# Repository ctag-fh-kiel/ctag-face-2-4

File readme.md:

CTAG face2|4 Audio Card, based on AD1938 codec
==============================================

This document includes board information, assembly guidelines, extensions and revision remarks, license and authors information.

Board information
-----------------
- 4 layer PCB including ground and power plane
- 10mil tracks offering close to 50Ohms impedance
- Part sizes on board are chosen to allow for hand-soldering 0603 as standard size for resistors etc.
- Used http://kicad.org/ for board design
- Board has 3 logical sections
  - Power supply (digital, analog)
     - Includes separate 3.3V digital supply and 3.3V + 5V analog supply
     - Includes boost converter that allows to run board on dual AA battery pack (3V input)
     - Standard input voltage at P201 should be +5V, see assembly options below
  - Codec including reset circuitry and digital I/O
  - Analog I/O
     - We checked several different single supply rail-to-rail OP Amps, where the cheap TLV272 performed pretty well, similar to the LMV722
- Codec and analog section is mainly based on Analog Devices reference design http://www.analog.com/media/en/technical-documentation/user-guides/UG-087.pdf

Assembly
-------------
- face2|4 BOM shared at Mouser
  - http://www.mouser.com/tools/projectcartsharing.aspx Access ID: 43007b9807
- Start with assembling the power supply sections
  - Several options for configuration are possible
     - A: Simplest possible, assemble only U203, U204, bypass U201 with JP201, bypass L202 with JP206, bypass L203 with JP207, assemble FB202, place JP204. Input voltage can be anything from 6-9V in this configuration.
     - B: No dedicated 3.3V digital do not assemble U202, assemble FB202, input voltage can be anything 2.4V-5V, boost converter will generate 5.5V for low-noise LDOs
     - C: With dedicated 3.3V digital supply, default in schematic, input voltage should be 5V
  - Check if power supply works by observing the LEDs
- Continue with codec, digital I/O and bias circuitry
  - Assembling only C311, C312 + JP301 is enough, using CM bias for test purposes
  - Test codec with microcontroller system, check at R602 R605 for signal output	
- Finally assemble analog section
  - May play around with some different OP amps

Extensions
-------------
- Created cape for Beagle Bone Green / Black including digital isolators to reduce noise (BBG-cape)
- Beagle Board X15 break out adapters for Hirose headers

Revisions
-------------
- face2|4
  - Rev. A2
     - Fixed polarity bug on IN2 at ADC2RP ADC2RN
    - Known Bugs: 
	 - none
	 - Rev. A has polarity bug on IN2
  - Todos for next Rev.
     - Possibly simplify power supply
     - Remove option to choose bias output from codec --> simplify board
	 - Option for balanced inputs
	 - Optimize pins on P1001 to improve routing, i.e. less vias on high speed digital lines, preserve impedance
- BBG-cape
  - Rev. A 
     - Initial Revision
    - Known Bugs: -
- X15 adaptor
  - Rev. A
     - Initial Revision, thanks to Michael Welling for review
	 
License
-------
This work is licensed under the Creative Commons Attribution-NonCommercial-ShareAlike 4.0 International License. 
To view a copy of this license, visit http://creativecommons.org/licenses/by-nc-sa/4.0/.
Anyone re-using this design needs to attribute to authors and http://www.creative-technologies.de website.

Authors
-------
- Robert Manzke (robert.manzke@fh-kiel.de), PCB Design
- Henrik Langer (henrik.langer@student.fh-kiel.de), Component Selection, Driver Development for Beagle Bone Series

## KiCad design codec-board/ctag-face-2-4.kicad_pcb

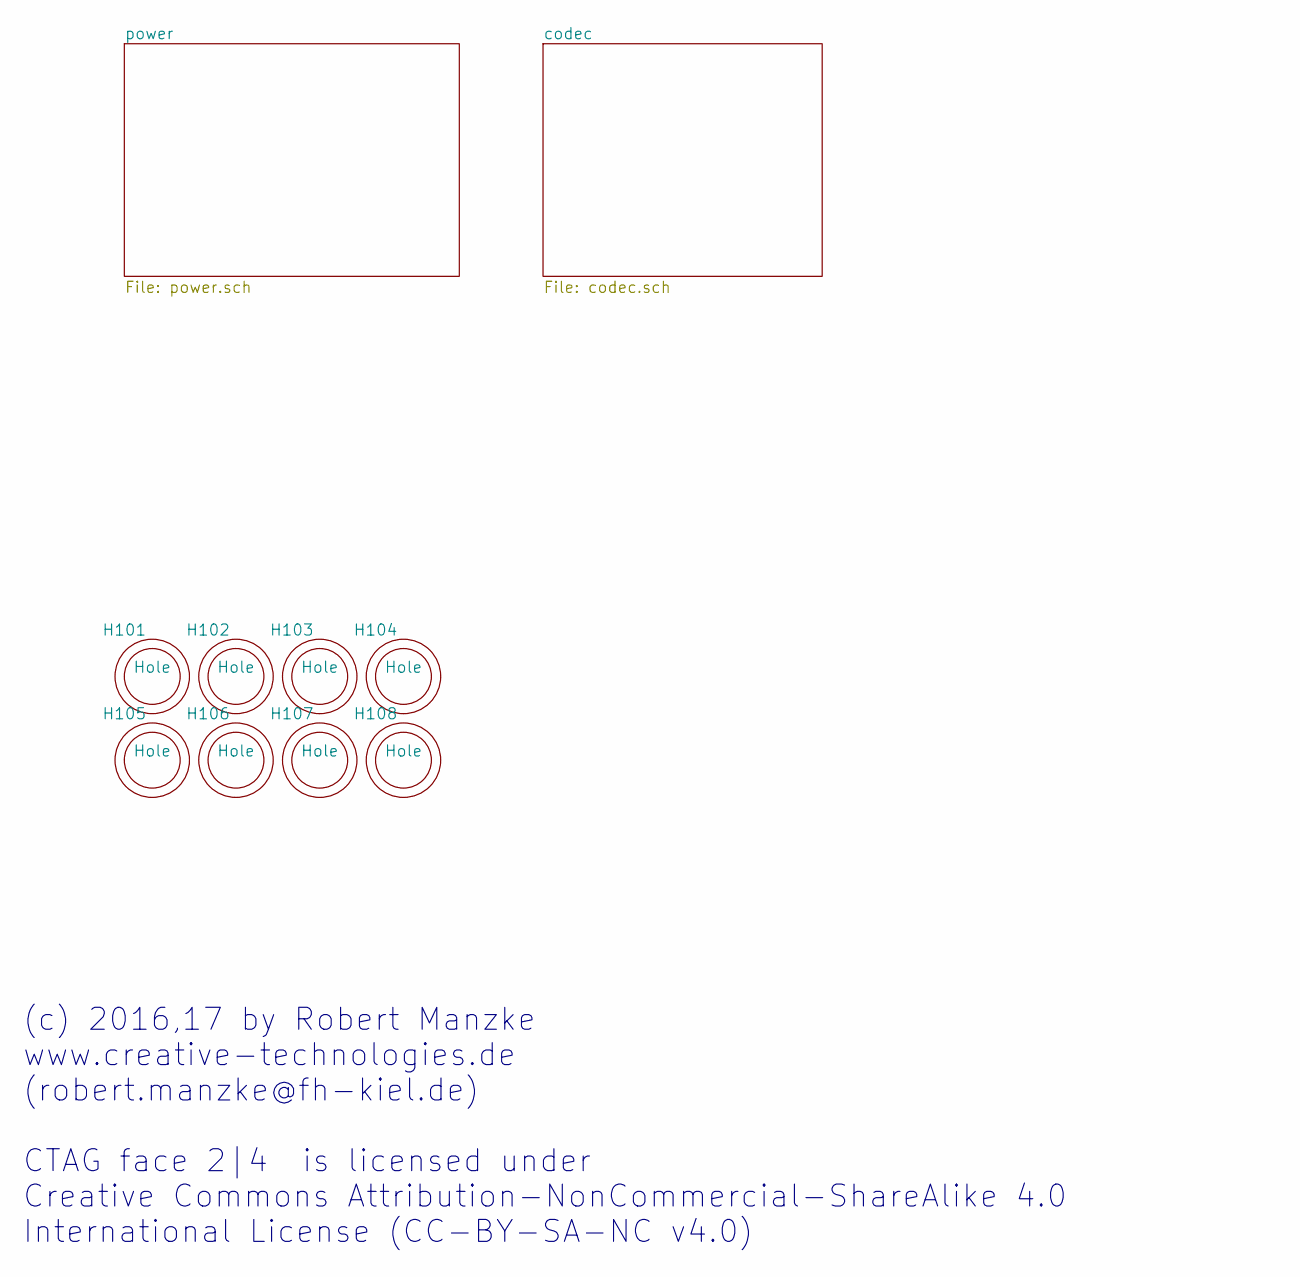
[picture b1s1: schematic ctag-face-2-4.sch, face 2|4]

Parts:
H101, H102, H103, H104, H105, H106, H107, H108: Hole; Hole_3mm

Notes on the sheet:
(c) 2016,17 by Robert Manzke www.creative-technologies.de (robert.manzke@fh-kiel.de) CTAG face 2|4 is licensed under Creative Commons Attribution-NonCommercial-ShareAlike 4.0 International License (CC-BY-SA-NC v4.0)

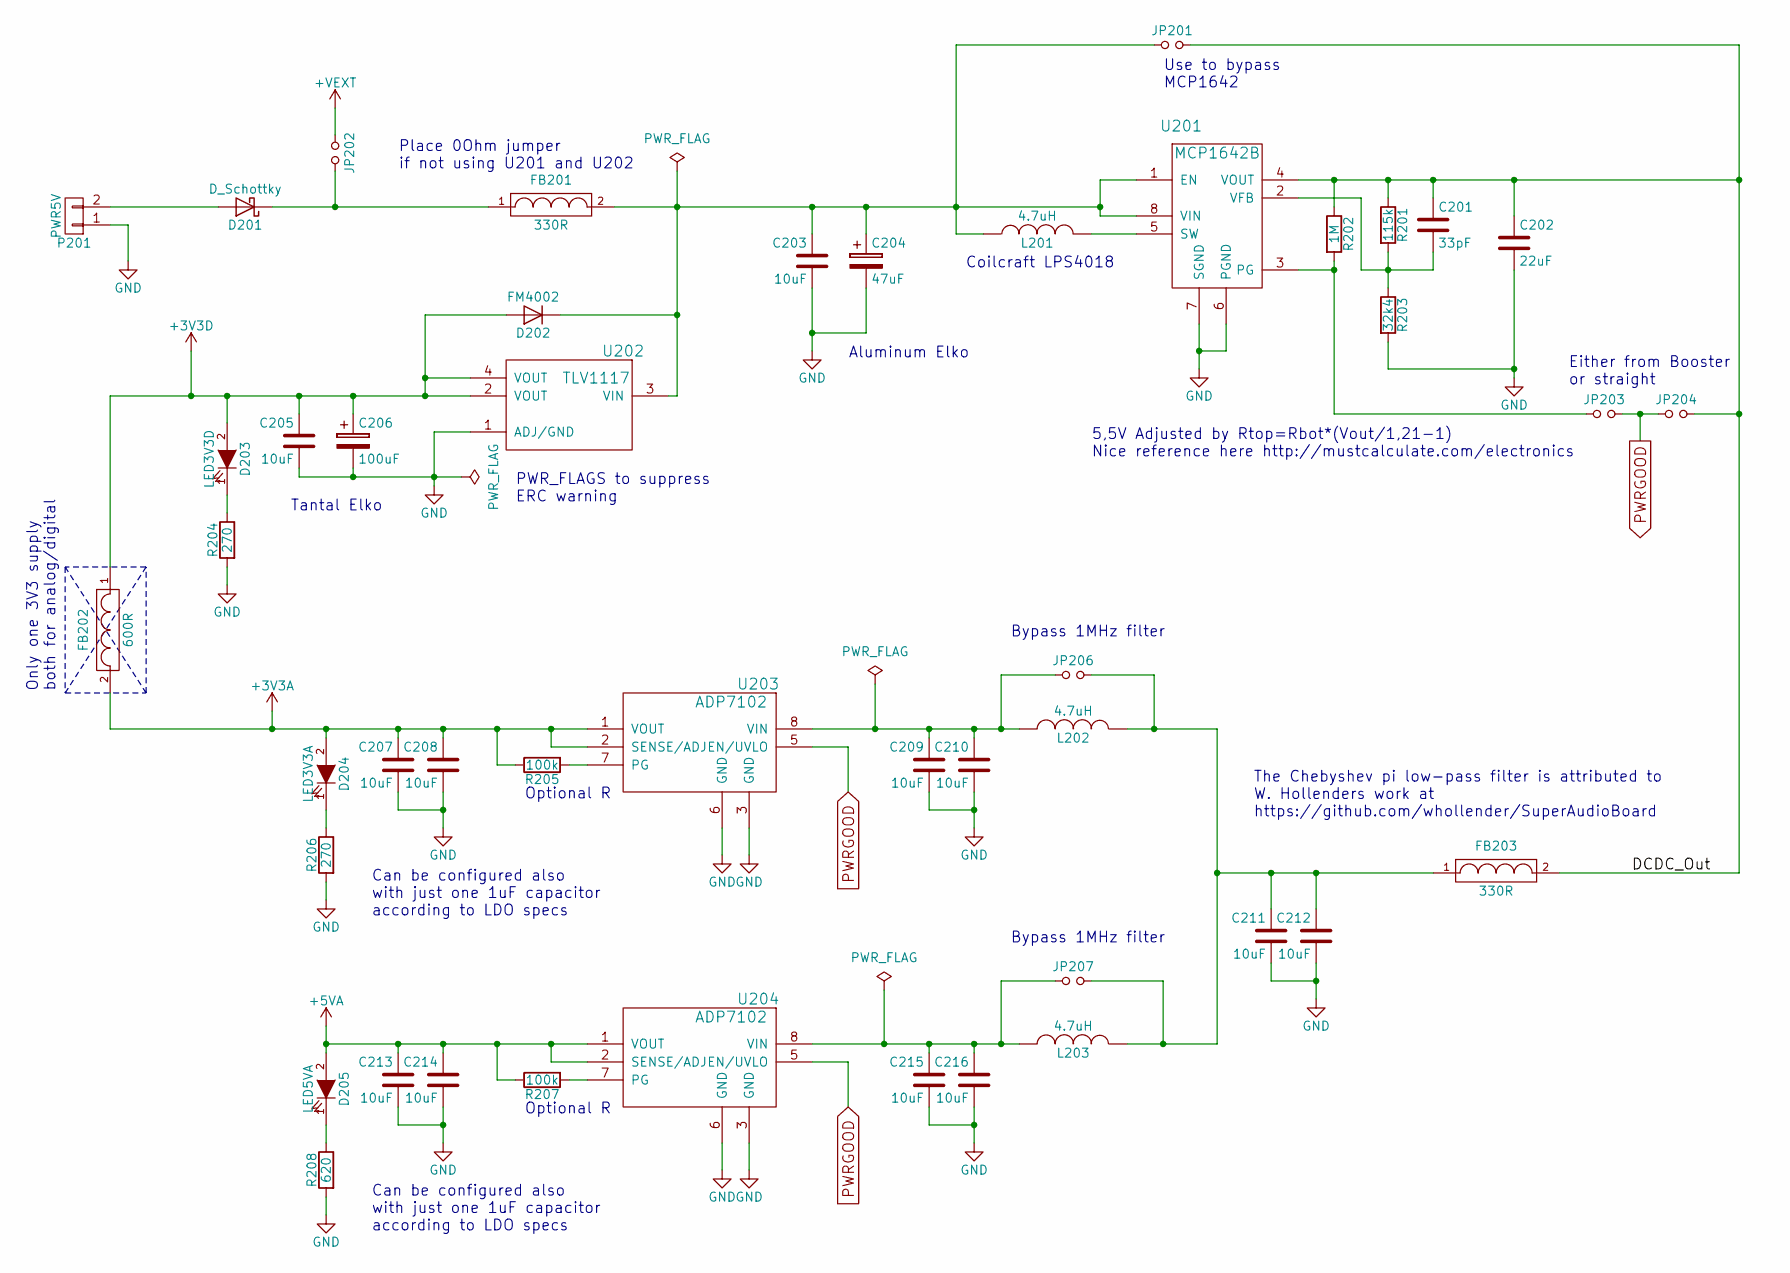
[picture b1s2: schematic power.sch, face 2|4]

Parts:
C201: 33pF; C_0603_HandSoldering
C202: 22uF; C_1210_HandSoldering
C203, C205, C207, C208, C209, C210, C211, C212, C213, C214, C215, C216: 10uF; C_1210_HandSoldering
C204: 47uF; c_elec_6.3x5.7
C206: 100uF; TantalC_SizeB_EIA-3528_HandSoldering
D201: D_Schottky; SOD-123
D202: FM4002; Diode-Universal-SMA-SMB_Handsoldering
D203: LED3V3D; LED-1206
D204: LED3V3A; LED-1206
D205: LED5VA; LED-1206
FB201, FB203: 330R; R_0805_HandSoldering
FB202: 600R; R_0805_HandSoldering
JP201, JP206, JP207: Jumper_NO_Small; R_0805_HandSoldering
JP202: Jumper_NO_Small; Pin_Header_Straight_1x02
JP203, JP204: Jumper_NO_Small; R_0603_HandSoldering
L201, L202, L203: 4.7uH; LPS4018
P201: PWR5V; Pin_Header_Straight_1x02
R201: 115k; R_0603_HandSoldering
R202: 1M; R_0603_HandSoldering
R203: 32k4; R_0603_HandSoldering
R204, R206: 270; R_0603_HandSoldering
R205, R207: 100k; R_0603_HandSoldering
R208: 620; R_0603_HandSoldering
U201: MCP1642B; MSOP-8_3x3mm_Pitch0.65mm
U202: TLV1117; SOT-223
U203, U204: ADP7102; SOIC-8_3.9x4.9mm_Pitch1.27mm

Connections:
+3V3A: C207.1, C208.1, D204.2 (A), FB202.2, R205.1, U203.1 (VOUT), U203.2 (SENSE/ADJ); also elsewhere on the board
+3V3D: C205.1, C206.1, D202.2 (A), D203.2 (A), FB202.1, U202.2 (VOUT), U202.4 (VOUT); also elsewhere on the board
+5VA: C213.1, C214.1, D205.2 (A), R207.1, U204.1 (VOUT), U204.2 (SENSE/ADJ); also elsewhere on the board
+VEXT: JP202.1; also elsewhere on the board
/power/DCDC_Out: C201.1, C202.1, FB203.2, JP201.2, JP204.2, R201.1, R202.1, U201.4 (VOUT)
GND: C202.2, C203.2, C204.2, C205.2, C206.2, C207.2, C208.2, C209.2, C210.2, C211.2, C212.2, C213.2, C214.2, C215.2, C216.2, P201.1, R203.2, R204.2, R206.2, R208.2, U201.6 (PGND), U201.7 (SGND), U202.1 (ADJ/GND), U203.3 (GND), U203.6 (GND), U204.3 (GND), U204.6 (GND); also elsewhere on the board
unnamed: C201.2, R201.2, R203.1, U201.2 (VFB)
unnamed: C203.1, C204.1, D202.1 (K), FB201.2, JP201.1, L201.1, U201.1 (EN), U201.8 (VIN), U202.3 (VIN)
unnamed: C209.1, C210.1, JP206.1, L202.2, U203.8 (VIN)
unnamed: C211.1, C212.1, FB203.1, JP206.2, JP207.2, L202.1, L203.1
unnamed: C215.1, C216.1, JP207.1, L203.2, U204.8 (VIN)
unnamed: D201.1 (K), FB201.1, JP202.2
unnamed: D201.2 (A), P201.2
unnamed: D203.1 (K), R204.1
unnamed: D204.1 (K), R206.1
unnamed: D205.1 (K), R208.1
unnamed: JP203.1, R202.2, U201.3 (PG)
unnamed: L201.2, U201.5 (SW)
unnamed: R205.2, U203.7 (PG)
unnamed: R207.2, U204.7 (PG)
PWRGOOD: JP203.2, JP204.1, U203.5 (EN/UVLO), U204.5 (EN/UVLO)

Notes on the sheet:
5,5V Adjusted by Rtop=Rbot*(Vout/1,21-1) Nice reference here http://mustcalculate.com/electronics
Tantal Elko
Aluminum Elko
PWR_FLAGS to suppress ERC warning
Use to bypass MCP1642
Bypass 1MHz filter
Only one 3V3 supply both for analog/digital
Optional R
Either from Booster or straight
Coilcraft LPS4018
Place 0Ohm jumper if not using U201 and U202
The Chebyshev pi low-pass filter is attributed to W. Hollenders work at https://github.com/whollender/SuperAudioBoard
Can be configured also with just one 1uF capacitor according to LDO specs

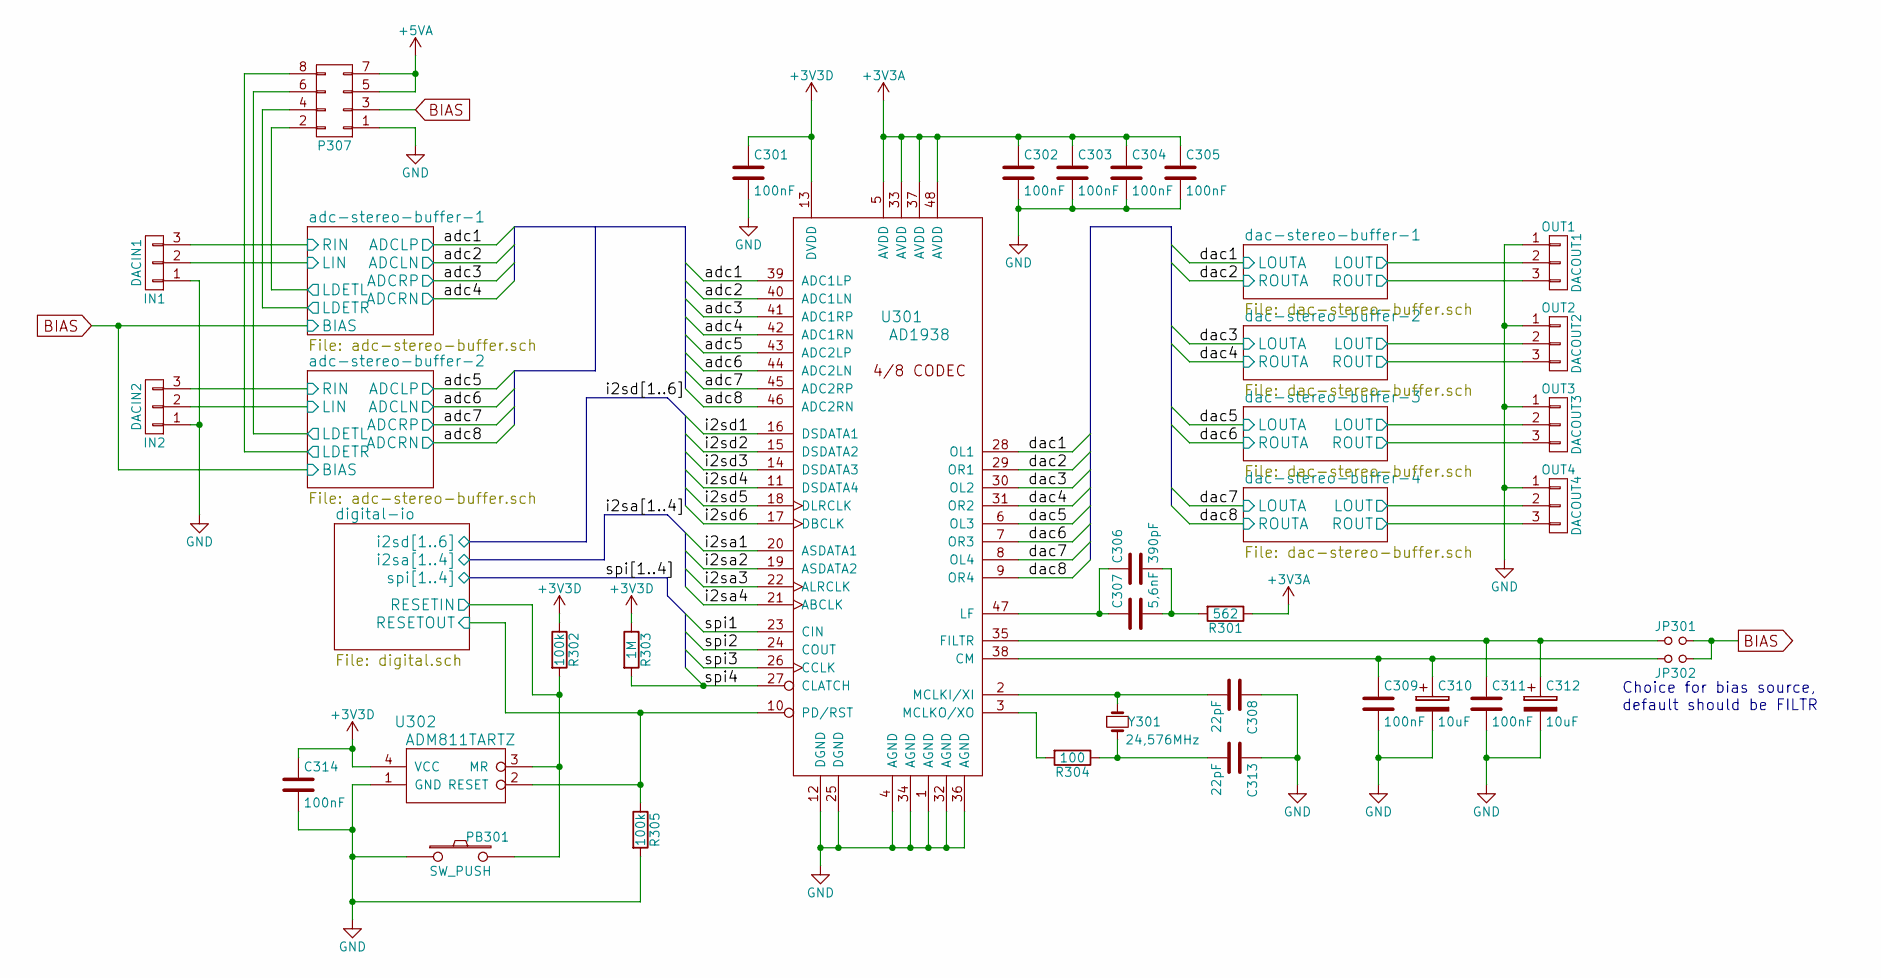
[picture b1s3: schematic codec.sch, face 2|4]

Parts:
C301, C302, C303, C304, C305, C309, C311, C314: 100nF; C_0603_HandSoldering
C306: 390pF; C_0603_HandSoldering
C307: 5,6nF; C_0603_HandSoldering
C308, C313: 22pF; C_0603_HandSoldering
C310, C312: 10uF; c_elec_4x5.7
IN1: DACIN1; Pin_Header_Straight_1x03
IN2: DACIN2; Pin_Header_Straight_1x03
JP301, JP302: Jumper_NO_Small; R_0603_HandSoldering
OUT1: DACOUT1; Pin_Header_Straight_1x03
OUT2: DACOUT2; Pin_Header_Straight_1x03
OUT3: DACOUT3; Pin_Header_Straight_1x03
OUT4: DACOUT4; Pin_Header_Straight_1x03
P307: Pin_Header_Straight_2x04
PB301: SW_PUSH; SW_SPST_PTS645
R301: 562; R_0603_HandSoldering
R302, R305: 100k; R_0603_HandSoldering
R303: 1M; R_0603_HandSoldering
R304: 100; R_0603_HandSoldering
U301: AD1938; LQFP-48_7x7mm_Pitch0.5mm
U302: ADM811TARTZ; SOT-143
Y301: 24,576MHz; Q_49U3HMS

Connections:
+3V3A: C302.1, C303.1, C304.1, C305.1, R301.1, U301.5 (AVDD), U301.33 (AVDD), U301.37 (AVDD), U301.48 (AVDD); also elsewhere on the board
+3V3D: C301.1, C314.1, R302.1, R303.1, U301.13 (DVDD), U302.4 (VCC); also elsewhere on the board
+5VA: P307.5, P307.7; also elsewhere on the board
/codec/adc1: U301.39 (ADC1LP); also elsewhere on the board
/codec/adc2: U301.40 (ADC1LN); also elsewhere on the board
/codec/adc3: U301.41 (ADC1RP); also elsewhere on the board
/codec/adc4: U301.42 (ADC1RN); also elsewhere on the board
/codec/adc5: U301.43 (ADC2LP); also elsewhere on the board
/codec/adc6: U301.44 (ADC2LN); also elsewhere on the board
/codec/adc7: U301.45 (ADC2RP); also elsewhere on the board
/codec/adc8: U301.46 (ADC2RN); also elsewhere on the board
/codec/adc-stereo-buffer-1/LDETL: P307.2; also elsewhere on the board
/codec/adc-stereo-buffer-1/LDETR: P307.4; also elsewhere on the board
/codec/adc-stereo-buffer-1/LIN: IN1.2; also elsewhere on the board
/codec/adc-stereo-buffer-1/RIN: IN1.3; also elsewhere on the board
/codec/adc-stereo-buffer-2/LDETL: P307.6; also elsewhere on the board
/codec/adc-stereo-buffer-2/LDETR: P307.8; also elsewhere on the board
/codec/adc-stereo-buffer-2/LIN: IN2.2; also elsewhere on the board
/codec/adc-stereo-buffer-2/RIN: IN2.3; also elsewhere on the board
/codec/dac1: U301.28 (OL1); also elsewhere on the board
/codec/dac2: U301.29 (OR1); also elsewhere on the board
/codec/dac3: U301.30 (OL2); also elsewhere on the board
/codec/dac4: U301.31 (OR2); also elsewhere on the board
/codec/dac5: U301.6 (OL3); also elsewhere on the board
/codec/dac6: U301.7 (OR3); also elsewhere on the board
/codec/dac7: U301.8 (OL4); also elsewhere on the board
/codec/dac8: U301.9 (OR4); also elsewhere on the board
/codec/dac-stereo-buffer-1/LOUT: OUT1.2; also elsewhere on the board
/codec/dac-stereo-buffer-1/ROUT: OUT1.3; also elsewhere on the board
/codec/dac-stereo-buffer-2/LOUT: OUT2.2; also elsewhere on the board
/codec/dac-stereo-buffer-2/ROUT: OUT2.3; also elsewhere on the board
/codec/dac-stereo-buffer-3/LOUT: OUT3.2; also elsewhere on the board
/codec/dac-stereo-buffer-3/ROUT: OUT3.3; also elsewhere on the board
/codec/dac-stereo-buffer-4/LOUT: OUT4.2; also elsewhere on the board
/codec/dac-stereo-buffer-4/ROUT: OUT4.3; also elsewhere on the board
/codec/digital-io/RESETIN: PB301.2, R302.2, U302.3 (MR); also elsewhere on the board
/codec/digital-io/RESETOUT: R305.1, U301.10 (PD/RST), U302.2 (RESET); also elsewhere on the board
/codec/i2sa1: U301.20 (ASDATA1); also elsewhere on the board
/codec/i2sa2: U301.19 (ASDATA2); also elsewhere on the board
/codec/i2sa3: U301.22 (ALRCLK); also elsewhere on the board
/codec/i2sa4: U301.21 (ABCLK); also elsewhere on the board
/codec/i2sd1: U301.16 (DSDATA1); also elsewhere on the board
/codec/i2sd2: U301.15 (DSDATA2); also elsewhere on the board
/codec/i2sd3: U301.14 (DSDATA3); also elsewhere on the board
/codec/i2sd4: U301.11 (DSDATA4); also elsewhere on the board
/codec/i2sd5: U301.18 (DLRCLK); also elsewhere on the board
/codec/i2sd6: U301.17 (DBCLK); also elsewhere on the board
/codec/spi1: U301.23 (CIN); also elsewhere on the board
/codec/spi2: U301.24 (COUT); also elsewhere on the board
/codec/spi3: U301.26 (CCLK); also elsewhere on the board
/codec/spi4: R303.2, U301.27 (CLATCH); also elsewhere on the board
BIAS: JP301.2, JP302.1, P307.3; also elsewhere on the board
GND: C301.2, C302.2, C303.2, C304.2, C305.2, C308.1, C309.2, C310.2, C311.2, C312.2, C313.1, C314.2, IN1.1, IN2.1, OUT1.1, OUT2.1, OUT3.1, OUT4.1, P307.1, PB301.1, R305.2, U301.1 (AGND), U301.4 (AGND), U301.12 (DGND), U301.25 (DGND), U301.32 (AGND), U301.34 (AGND), U301.36 (AGND), U302.1 (GND); also elsewhere on the board
unnamed: C306.1, C307.1, U301.47 (LF)
unnamed: C306.2, C307.2, R301.2
unnamed: C308.2, U301.2 (MCLKI/XI), Y301.1
unnamed: C309.1, C310.1, JP302.2, U301.38 (CM)
unnamed: C311.1, C312.1, JP301.1, U301.35 (FILTR)
unnamed: C313.2, R304.1, Y301.2
unnamed: R304.2, U301.3 (MCLKO/XO)

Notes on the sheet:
Choice for bias source, default should be FILTR

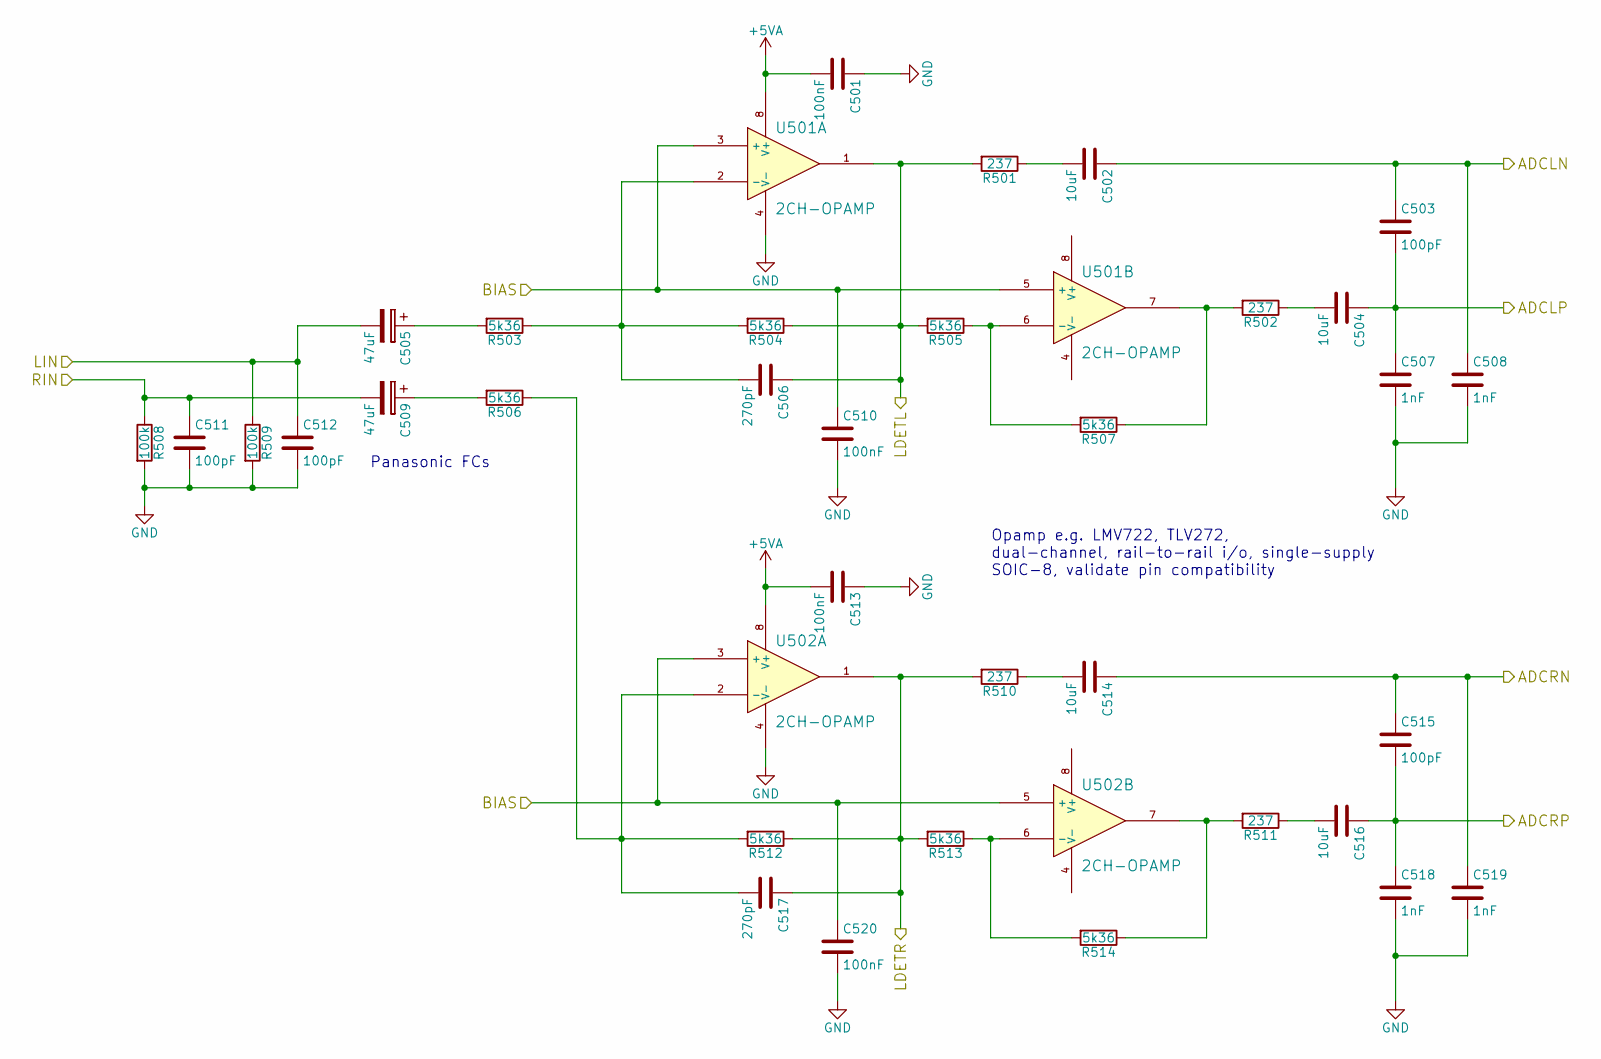
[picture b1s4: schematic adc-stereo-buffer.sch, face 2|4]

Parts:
C401, C410, C413, C420: 100nF; C_0603_HandSoldering
C402, C404, C414, C416: 10uF; C_0805_HandSoldering
C403, C411, C412, C415: 100pF; C_0603_HandSoldering
C405, C409: 47uF; c_elec_6.3x5.7
C406, C417: 270pF; C_0603_HandSoldering
C407, C408, C418, C419: 1nF; C_0603_HandSoldering
R401, R402, R410, R411: 237; R_0603_HandSoldering
R403, R404, R405, R406, R407, R412, R413, R414: 5k36; R_0603_HandSoldering
R408, R409: 100k; R_0603_HandSoldering
U401, U402: 2CH-OPAMP; SOIC-8_3.9x4.9mm_Pitch1.27mm

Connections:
+5VA: C401.2, C413.2, U401.8 (V+), U402.8 (V+); also elsewhere on the board
/codec/adc1: C403.2, C404.1, C407.1; also elsewhere on the board
/codec/adc2: C402.1, C403.1, C408.1; also elsewhere on the board
/codec/adc3: C415.2, C416.1, C418.1; also elsewhere on the board
/codec/adc4: C414.1, C415.1, C419.1; also elsewhere on the board
/codec/adc-stereo-buffer-1/LDETL: C406.1, R401.2, R404.1, R405.2, U401.1; also elsewhere on the board
/codec/adc-stereo-buffer-1/LDETR: C417.1, R410.2, R412.1, R413.2, U402.1; also elsewhere on the board
/codec/adc-stereo-buffer-1/LIN: C405.2, C412.1, R409.1; also elsewhere on the board
/codec/adc-stereo-buffer-1/RIN: C409.2, C411.1, R408.1; also elsewhere on the board
BIAS: C410.1, C420.1, U401.3 (+), U401.5 (+), U402.3 (+), U402.5 (+); also elsewhere on the board
GND: C401.1, C407.2, C408.2, C410.2, C411.2, C412.2, C413.1, C418.2, C419.2, C420.2, R408.2, R409.2, U401.4 (V-), U402.4 (V-); also elsewhere on the board
unnamed: C402.2, R401.1
unnamed: C404.2, R402.1
unnamed: C405.1, R403.2
unnamed: C406.2, R403.1, R404.2, U401.2 (-)
unnamed: C409.1, R406.2
unnamed: C414.2, R410.1
unnamed: C416.2, R411.1
unnamed: C417.2, R406.1, R412.2, U402.2 (-)
unnamed: R402.2, R407.1, U401.7
unnamed: R405.1, R407.2, U401.6 (-)
unnamed: R411.2, R414.1, U402.7
unnamed: R413.1, R414.2, U402.6 (-)

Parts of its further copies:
C501, C510, C513, C520: 100nF; C_0603_HandSoldering
C502, C504, C514, C516: 10uF; C_0805_HandSoldering
C503, C511, C512, C515: 100pF; C_0603_HandSoldering
C505, C509: 47uF; c_elec_6.3x5.7
C506, C517: 270pF; C_0603_HandSoldering
C507, C508, C518, C519: 1nF; C_0603_HandSoldering
R501, R502, R510, R511: 237; R_0603_HandSoldering
R503, R504, R505, R506, R507, R512, R513, R514: 5k36; R_0603_HandSoldering
R508, R509: 100k; R_0603_HandSoldering
U501, U502: 2CH-OPAMP; SOIC-8_3.9x4.9mm_Pitch1.27mm

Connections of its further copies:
+5VA: C501.2, C513.2, U501.8 (V+), U502.8 (V+); also elsewhere on the board
/codec/adc5: C503.2, C504.1, C507.1; also elsewhere on the board
/codec/adc6: C502.1, C503.1, C508.1; also elsewhere on the board
/codec/adc7: C515.2, C516.1, C518.1; also elsewhere on the board
/codec/adc8: C514.1, C515.1, C519.1; also elsewhere on the board
/codec/adc-stereo-buffer-2/LDETL: C506.1, R501.2, R504.1, R505.2, U501.1; also elsewhere on the board
/codec/adc-stereo-buffer-2/LDETR: C517.1, R510.2, R512.1, R513.2, U502.1; also elsewhere on the board
/codec/adc-stereo-buffer-2/LIN: C505.2, C512.1, R509.1; also elsewhere on the board
/codec/adc-stereo-buffer-2/RIN: C509.2, C511.1, R508.1; also elsewhere on the board
BIAS: C510.1, C520.1, U501.3 (+), U501.5 (+), U502.3 (+), U502.5 (+); also elsewhere on the board
GND: C501.1, C507.2, C508.2, C510.2, C511.2, C512.2, C513.1, C518.2, C519.2, C520.2, R508.2, R509.2, U501.4 (V-), U502.4 (V-); also elsewhere on the board
unnamed: C502.2, R501.1
unnamed: C504.2, R502.1
unnamed: C505.1, R503.2
unnamed: C506.2, R503.1, R504.2, U501.2 (-)
unnamed: C509.1, R506.2
unnamed: C514.2, R510.1
unnamed: C516.2, R511.1
unnamed: C517.2, R506.1, R512.2, U502.2 (-)
unnamed: R502.2, R507.1, U501.7
unnamed: R505.1, R507.2, U501.6 (-)
unnamed: R511.2, R514.1, U502.7
unnamed: R513.1, R514.2, U502.6 (-)

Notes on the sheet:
Opamp e.g. LMV722, TLV272, dual-channel, rail-to-rail i/o, single-supply SOIC-8, validate pin compatibility
Panasonic FCs

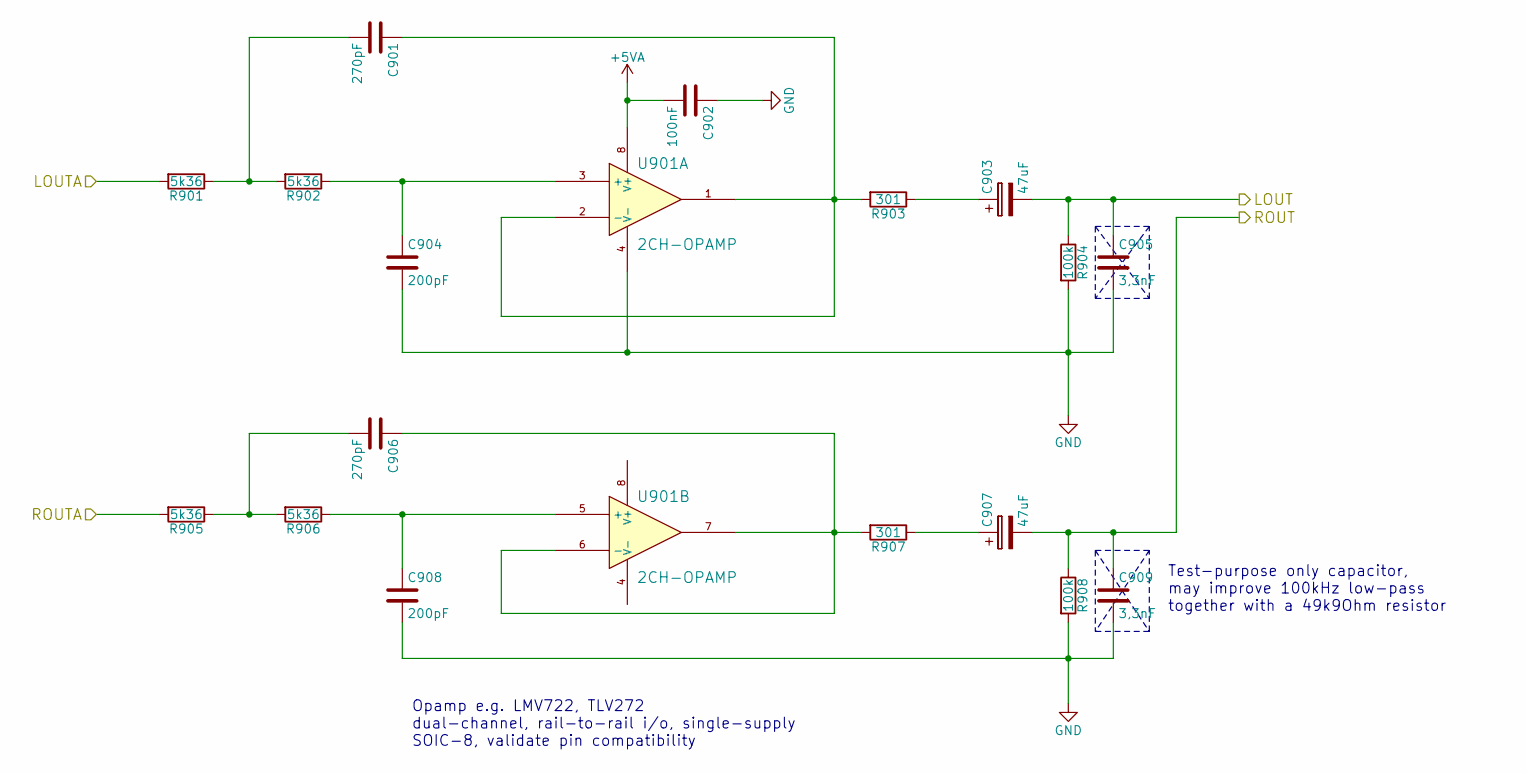
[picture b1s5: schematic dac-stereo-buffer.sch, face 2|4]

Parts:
C601, C606: 270pF; C_0603_HandSoldering
C602: 100nF; C_0603_HandSoldering
C603, C607: 47uF; c_elec_6.3x5.7
C604, C608: 200pF; C_0603_HandSoldering
C605, C609: 3,3nF; C_0603_HandSoldering
R601, R602, R605, R606: 5k36; R_0603_HandSoldering
R603, R607: 301; R_0603_HandSoldering
R604, R608: 100k; R_0603_HandSoldering
U601: 2CH-OPAMP; SOIC-8_3.9x4.9mm_Pitch1.27mm

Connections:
+5VA: C602.2, U601.8 (V+); also elsewhere on the board
/codec/dac1: R601.2; also elsewhere on the board
/codec/dac2: R605.2; also elsewhere on the board
/codec/dac-stereo-buffer-1/LOUT: C603.2, C605.1, R604.1; also elsewhere on the board
/codec/dac-stereo-buffer-1/ROUT: C607.2, C609.1, R608.1; also elsewhere on the board
GND: C602.1, C604.2, C605.2, C608.2, C609.2, R604.2, R608.2, U601.4 (V-); also elsewhere on the board
unnamed: C601.1, R603.2, U601.1, U601.2 (-)
unnamed: C601.2, R601.1, R602.2
unnamed: C603.1, R603.1
unnamed: C604.1, R602.1, U601.3 (+)
unnamed: C606.1, R607.2, U601.6 (-), U601.7
unnamed: C606.2, R605.1, R606.2
unnamed: C607.1, R607.1
unnamed: C608.1, R606.1, U601.5 (+)

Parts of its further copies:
C701, C706, C801, C806, C901, C906: 270pF; C_0603_HandSoldering
C702, C802, C902: 100nF; C_0603_HandSoldering
C703, C707, C803, C807, C903, C907: 47uF; c_elec_6.3x5.7
C704, C708, C804, C808, C904, C908: 200pF; C_0603_HandSoldering
C705, C709, C805, C809, C905, C909: 3,3nF; C_0603_HandSoldering
R701, R702, R705, R706, R801, R802, R805, R806, R901, R902, R905, R906: 5k36; R_0603_HandSoldering
R703, R707, R803, R807, R903, R907: 301; R_0603_HandSoldering
R704, R708, R804, R808, R904, R908: 100k; R_0603_HandSoldering
U701, U801, U901: 2CH-OPAMP; SOIC-8_3.9x4.9mm_Pitch1.27mm

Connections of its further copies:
+5VA: C702.2, C802.2, C902.2, U701.8 (V+), U801.8 (V+), U901.8 (V+); also elsewhere on the board
/codec/dac3: R701.2; also elsewhere on the board
/codec/dac4: R705.2; also elsewhere on the board
/codec/dac5: R801.2; also elsewhere on the board
/codec/dac6: R805.2; also elsewhere on the board
/codec/dac7: R901.2; also elsewhere on the board
/codec/dac8: R905.2; also elsewhere on the board
/codec/dac-stereo-buffer-2/LOUT: C703.2, C705.1, R704.1; also elsewhere on the board
/codec/dac-stereo-buffer-2/ROUT: C707.2, C709.1, R708.1; also elsewhere on the board
/codec/dac-stereo-buffer-3/LOUT: C803.2, C805.1, R804.1; also elsewhere on the board
/codec/dac-stereo-buffer-3/ROUT: C807.2, C809.1, R808.1; also elsewhere on the board
/codec/dac-stereo-buffer-4/LOUT: C903.2, C905.1, R904.1; also elsewhere on the board
/codec/dac-stereo-buffer-4/ROUT: C907.2, C909.1, R908.1; also elsewhere on the board
GND: C702.1, C704.2, C705.2, C708.2, C709.2, C802.1, C804.2, C805.2, C808.2, C809.2, C902.1, C904.2, C905.2, C908.2, C909.2, R704.2, R708.2, R804.2, R808.2, R904.2, R908.2, U701.4 (V-), U801.4 (V-), U901.4 (V-); also elsewhere on the board
unnamed: C701.1, R703.2, U701.1, U701.2 (-)
unnamed: C701.2, R701.1, R702.2
unnamed: C703.1, R703.1
unnamed: C704.1, R702.1, U701.3 (+)
unnamed: C706.1, R707.2, U701.6 (-), U701.7
unnamed: C706.2, R705.1, R706.2
unnamed: C707.1, R707.1
unnamed: C708.1, R706.1, U701.5 (+)
unnamed: C801.1, R803.2, U801.1, U801.2 (-)
unnamed: C801.2, R801.1, R802.2
unnamed: C803.1, R803.1
unnamed: C804.1, R802.1, U801.3 (+)
unnamed: C806.1, R807.2, U801.6 (-), U801.7
unnamed: C806.2, R805.1, R806.2
unnamed: C807.1, R807.1
unnamed: C808.1, R806.1, U801.5 (+)
unnamed: C901.1, R903.2, U901.1, U901.2 (-)
unnamed: C901.2, R901.1, R902.2
unnamed: C903.1, R903.1
unnamed: C904.1, R902.1, U901.3 (+)
unnamed: C906.1, R907.2, U901.6 (-), U901.7
unnamed: C906.2, R905.1, R906.2
unnamed: C907.1, R907.1
unnamed: C908.1, R906.1, U901.5 (+)

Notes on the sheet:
Opamp e.g. LMV722, TLV272 dual-channel, rail-to-rail i/o, single-supply SOIC-8, validate pin compatibility
Test-purpose only capacitor, may improve 100kHz low-pass together with a 49k9Ohm resistor

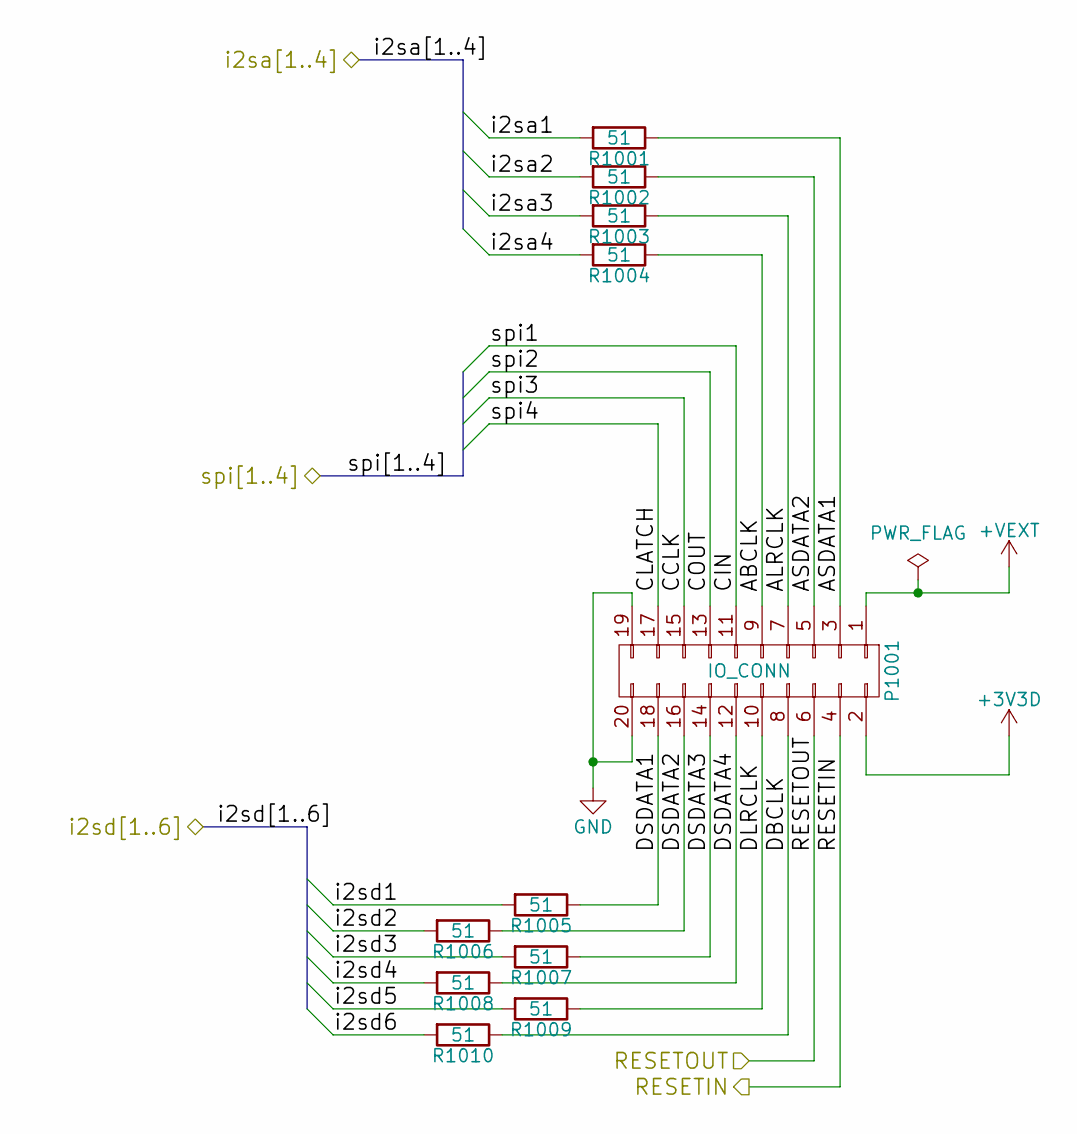
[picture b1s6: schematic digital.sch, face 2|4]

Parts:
P1001: IO_CONN; Pin_Header_Straight_2x10
R1001, R1002, R1003, R1004, R1005, R1006, R1007, R1008, R1009, R1010: 51; R_0603_HandSoldering

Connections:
+3V3D: P1001.2; also elsewhere on the board
+VEXT: P1001.1; also elsewhere on the board
/codec/digital-io/ABCLK: P1001.9, R1004.1
/codec/digital-io/ALRCLK: P1001.7, R1003.1
/codec/digital-io/ASDATA1: P1001.3, R1001.1
/codec/digital-io/ASDATA2: P1001.5, R1002.1
/codec/digital-io/DBCLK: P1001.8, R1010.1
/codec/digital-io/DLRCLK: P1001.10, R1009.1
/codec/digital-io/DSDATA1: P1001.18, R1005.1
/codec/digital-io/DSDATA2: P1001.16, R1006.1
/codec/digital-io/DSDATA3: P1001.14, R1007.1
/codec/digital-io/DSDATA4: P1001.12, R1008.1
/codec/digital-io/RESETIN: P1001.4; also elsewhere on the board
/codec/digital-io/RESETOUT: P1001.6; also elsewhere on the board
/codec/i2sa1: R1001.2; also elsewhere on the board
/codec/i2sa2: R1002.2; also elsewhere on the board
/codec/i2sa3: R1003.2; also elsewhere on the board
/codec/i2sa4: R1004.2; also elsewhere on the board
/codec/i2sd1: R1005.2; also elsewhere on the board
/codec/i2sd2: R1006.2; also elsewhere on the board
/codec/i2sd3: R1007.2; also elsewhere on the board
/codec/i2sd4: R1008.2; also elsewhere on the board
/codec/i2sd5: R1009.2; also elsewhere on the board
/codec/i2sd6: R1010.2; also elsewhere on the board
/codec/spi1: P1001.11; also elsewhere on the board
/codec/spi2: P1001.13; also elsewhere on the board
/codec/spi3: P1001.15; also elsewhere on the board
/codec/spi4: P1001.17; also elsewhere on the board
GND: P1001.19, P1001.20; also elsewhere on the board

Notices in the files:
codec-board/ctag-face-2-4.kicad_pcb:
(c) 2017 Rev. A2
extension-capes/bbg-adaptor/bbg-adaptor.kicad_pcb:
(c) 2016, Rev. A
